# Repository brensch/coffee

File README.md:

# coffee

An espresso machine controller built emulation-first, in Rust. It's in the spirit of GaggiMate/Gaggiuino, with these differences:

- **One product, two shells.** Everything the machine does (engine, profiles, shot history, the whole HTTP API, logging) lives in the `no_std` crate `coffee-node`. The PC binary and the ESP32 firmware are thin wrappers that differ only in plumbing.
- **A physics emulator stands in for the machine.** It models the boiler and water thermals, the vibratory pump, the over-pressure valve, steam saturation, the puck, the cup and scale, and sensor quirks. It can inject faults and runs coupled in lockstep with the engine.
- **A scenario language scripts tests.** Timed and event-triggered actions, fault injection and expectations make a CI suite: 19 scenarios, about 2.5 hours of machine time in about 80 s.
- **Real-machine logs calibrate the model.** PC and firmware write the same compact binary log of the hardware boundary (`.clog`, about 2.7 bytes per tick, about 1 MB per machine-hour). `coffee-emu fit` replays it and adjusts model parameters until the simulated sensors match.
- **The web UI is all Rust (Leptos).**
  - **Machine** page: everything live from telemetry (same on the ESP32), including an animated machine diagram, shot chart, controls and temperature.
  - **Experiments**: emulator ground truth beside what the engine believes, fault injection, scenarios, model parameters.
  - Profiles, History (grind advice against a reference shot) and Settings.
  - Brewing is refused until the machine is Ready (water at temperature, group heat-soaked) unless you choose *Brew anyway*. The physical switch always works.

Target machine: **Gaggia Classic Pro E24, US 120 V / 60 Hz** only (model: `models/gaggia_classic_pro_e24_120v.toml`). See [docs/HARDWARE.md](docs/HARDWARE.md).

## Quick start

```sh
cargo build --release                       # engine, emulator, tools
(cd ui && trunk build --release)            # web UI (needs `trunk`, wasm32 target)

./target/release/coffee-emu test            # run the scenario suite
./target/release/coffee-emu serve --spawn-engine
#   -> UI at http://127.0.0.1:8080  (Experiments tab drives the emulator)
```

Other things to try:

```sh
coffee-emu run scenarios/02_shot_classic.scn --trace out/shot.csv --events
coffee-emu signals                          # everything you can read / set / fit
coffee-emu fit --log real.clog --params thermal.boiler_mass_kg,thermal.loss_boiler_w_k --out models/mine.toml
coffee-emu import-gaggimate path/to/*.json  # convert GaggiMate profiles
coffee-emu import-decent path/to/*.tcl      # convert Decent Espresso profiles
python3 tools/profile_check.py profiles/community   # brew every profile in the emulator
```

Firmware: ESP32-C6 (stable Rust), flashed and provisioned with the `coffee` CLI (non-interactive, `--json`; see [firmware/esp32/README.md](firmware/esp32/README.md)):

```sh
coffee flash                                  # build + flash over USB (needs espflash)
coffee wifi set --ssid HomeNet --password ... # store Wi-Fi, wait for an IP
open http://coffee.local/                     # the same UI and API, served by the board
coffee ota --host coffee.local                # later updates over Wi-Fi: steam rocker on, then brew held 3 s
coffee-emu capture --port /dev/ttyACM0 --out real.clog   # record its log
coffee flash --bridge && coffee-emu serve --engine-serial /dev/ttyACM0   # hardware-in-the-loop
```

## Hardware: the v45 controller board

One 71.2 × 77 mm board, the Gaggiuino split done carefully, in a printed holder that sticks to the
side panel with magnets (hardware/holder). The pump, the 3-way valve and the board's own
supply are switched on the board, behind a 7 mm milled isolation band (7.83 mm minimum, verified on the
copper). The 11 A heater stays on a factory SSR on the rear panel. It carries:
- **Mains half:** four 6.3 mm spades (N, L, P, 3), a 2 A fuse, a certified Mean Well IRM-10-5, and two
  zero-cross opto-triac channels (T435 pump, T410 valve) with X2-rated snubbers;
- an ESP32-C6-MINI-1U (105 °C rated, W.FL / MHF III antenna connector);
- a K-type thermocouple front end (MCP3421 18-bit ADC + TMP117 cold junction), plus pressure, front-panel
  (three switches in, three LEDs out) and drip-tray scale inputs;
- **latching JST GH sockets, each lead a unique size**, so no lead fits another's socket (checked on every
  build: docs/SWAP-SAFETY.md), and a screw terminal for the thermocouple;
- mains spades along the top edge, low-voltage plugs along the bottom: the two bundles leave in opposite
  directions;
- USB-C for the first flash (then updates go over Wi-Fi), and a 7-LED indicator row: status, the three
  front-panel lamps, and heater/pump/valve.

| Item | What | Notes |
|---|---|---|
| Board | v45 controller, assembled by JLCPCB (full, nothing to solder; or SMD-only plus 6 parts to solder) | `hardware/controller` generates everything: schematic, PCB, DRC, isolation check, fab and JLC files. See [docs/CIRCUIT.md](docs/CIRCUIT.md). |
| Boiler temperature | K-type M4 screw-in thermocouple (Gaggiuino's) | NIST type-K conversion with cold-junction compensation in firmware. Two-point calibration. |
| Pressure | Transducer 0–1.2 MPa, 5 V, 0.5–4.5 V, G1/4 (Gaggiuino's) + [GaggiMate plumbing kit](https://shop.gaggimate.eu/products/gaggimate-plumbing-kit) | |
| Antenna | 2.4 GHz, W.FL (MHF III) pigtail, ≤ 2.33 dBi | Outside the steel case. |
| Scale *(optional)* | Two load cells under the drip tray, dual HX711, wired | Weight stop. See docs/CALIBRATION.md. |

The full list and the reasons behind it are in [docs/HARDWARE.md](docs/HARDWARE.md); fitting it is
[docs/INSTALL.md](docs/INSTALL.md). Off-the-shelf alternatives are compared in
[docs/OFF_THE_SHELF.md](docs/OFF_THE_SHELF.md).

**Keep in the machine:** the steam thermostat (or a 165–170 °C limiter) and the thermal fuse, in
series with the heater.

## Layout

| Path | What |
|---|---|
| `crates/coffee-io` | Hardware boundary: per-mains-cycle `SensorFrame` / `ActuatorFrame` (thermocouple µV, cold junction, pressure in ADC millivolts), lockstep wire protocol. `no_std`. |
| `crates/coffee-board` | Pure firmware logic, host-tested: crystal cycle clock, ADC oversampling, switch debounce, status LED, grid-drift stroke model. `no_std`. |
| `crates/coffee-core` | The engine: sensor conversion, filters, PID + feed-forward, pump-model flow linearisation, profiles, state machine, safety. `no_std + alloc`. |
| `crates/coffee-api` | HTTP/WS API types, shot recorder, grind advice, GaggiMate importer. Shared by engine, firmware and UI. |
| `crates/coffee-node` | **The product**: engine plus shot recorder, profile library (built-ins compiled in), config, the HTTP API as a pure function, telemetry, binary log (`tlog`) and shot (`shotpack`) formats. `no_std + alloc`. |
| `crates/coffee-engine` | PC shell: lockstep link (stdio / TCP), file storage (`--data`), axum passing `/api/*` to the node, UI hosting. |
| `crates/coffee-physics` | Coupled machine model with fault injection. Parameters live in `models/*.toml`. |
| `crates/coffee-scenario` | Scenario DSL: parser and runner. |
| `crates/coffee-emu` | Emulator suite: `run`, `test`, `serve` (live lab), `replay`, `fit`, `import-gaggimate`. |
| `ui/` | Leptos web UI. |
| `hardware/controller` | Controller board as code: SKiDL schematic with isolation and pin-map checks, KiCad layout with the mains lint, Freerouting, ngspice simulations, 3D renders, JLCPCB files, audit pack. |
| `tools/` | `iterate.sh`: rebuild, run diagnostic shots, print control-quality metrics. |
| `crates/coffee-cli` | `coffee`: flash, Wi-Fi provisioning, status, logs and OTA for the board. Non-interactive, `--json`, exit codes. |
| `firmware/esp32` | ESP32-C6 firmware: machine mode (control loop, Wi-Fi, embedded UI + API, flash storage, OTA, USB console) and USB bridge mode. |
| `models/`, `profiles/`, `scenarios/` | Machine models, shot profiles (built-ins + `profiles/community`: 47 Decent and 4 GaggiMate profiles, with their own licenses), test scenarios. |

Docs: [PROFILES](docs/PROFILES.md) · [ARCHITECTURE](docs/ARCHITECTURE.md) · [HARDWARE & BOM](docs/HARDWARE.md) · [CIRCUIT](docs/CIRCUIT.md) · [OFF-THE-SHELF](docs/OFF_THE_SHELF.md) · [INSTALL](docs/INSTALL.md) · [CALIBRATION](docs/CALIBRATION.md) · [MODELS](docs/MODELS.md) · [SCENARIOS](docs/SCENARIOS.md)

## Status

- **Working and tested in emulation:**
  - engine, physics, DSL, test suite
  - calibration loop (including a test that recovers known parameters from synthetic data)
  - live lab and UI
  - GaggiMate import
- **Compiles, not yet run on hardware:** ESP32-C6 firmware: machine mode (Wi-Fi, web UI and API, WebSocket telemetry, flash storage, OTA, USB provisioning) and bridge mode; the `coffee` CLI.
- **Designed, not yet reviewed or built:** the v6 controller board (routed, DRC-checked, simulated; audit pack in `hardware/controller/build/`).
- **Not built yet:**
  - a Bluetooth scale driver
  - the motorised grinder
- **Every model parameter is an estimate until fitted to logs from your machine.** See [docs/MODELS.md](docs/MODELS.md).

⚠️ This controls a mains-powered heater and a 15 bar pump. Keep the machine's hardware thermal protection in series. See the safety section in [docs/HARDWARE.md](docs/HARDWARE.md).

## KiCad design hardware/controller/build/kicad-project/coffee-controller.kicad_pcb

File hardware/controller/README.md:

# Controller board v2

One board that drives a Gaggia Classic Pro: an ESP32-S3, the 5 V supply, zero-cross sensing,
three zero-cross triacs (heater, pump, valve), and the thermocouple and pressure inputs. The mains
side and the SELV side are split by a 7 mm copper-free band with milled slots. The design and its
calculations are in [docs/CIRCUIT.md](../../docs/CIRCUIT.md), and the install plan is in
[docs/INSTALL.md](../../docs/INSTALL.md).

## Look at it
- `build/coffee-controller-120v.kicad_pcb`: open it in KiCad 7 or later.
- `build/coffee-controller-120v.png` / `.pdf` / `-top.svg` / `-bottom.svg`: quick views.
- `build/coffee-controller-120v-drc.rpt`: DRC report. 0 errors; the warnings left are
  silkscreen overlaps, two thermal-spoke counts and one dangling stub.
- `build/coffee-controller-120v-fab/`: gerbers, drill file and pick-and-place CSV.
- `build/bom-120v.csv`: the BOM.

## Rebuild
```sh
python3 -m venv .venv && .venv/bin/pip install -r requirements.txt
.venv/bin/python controller.py            # schematic: ERC + design checks -> netlist, BOM, parts.json
source ~/opt/kienv.sh && python3 layout.py # place, route (Freerouting, 90° corners), fill, DRC, fab outputs
MAINS_V=120 .venv/bin/python controller.py && python3 layout.py --mains 120
```

`layout.py` needs:
- **KiCad 7's pcbnew Python and footprint libraries.** No root access? Extract the Ubuntu debs:
  `apt-get download kicad kicad-footprints …`, then `dpkg -x` each one, then source an env file
  that sets `PYTHONPATH`, `LD_LIBRARY_PATH` and `KICAD7_FOOTPRINT_DIR`.
- **Freerouting 2.1.0** (`fr-2.1.0.jar`, Java 21). Don't use the 2.5.0 native CLI: it hangs at
  0% CPU after an internal crash.

**Status:** generated, routed and DRC-checked by code. Not yet reviewed by a person, and not yet
built. Review the mains side before ordering.

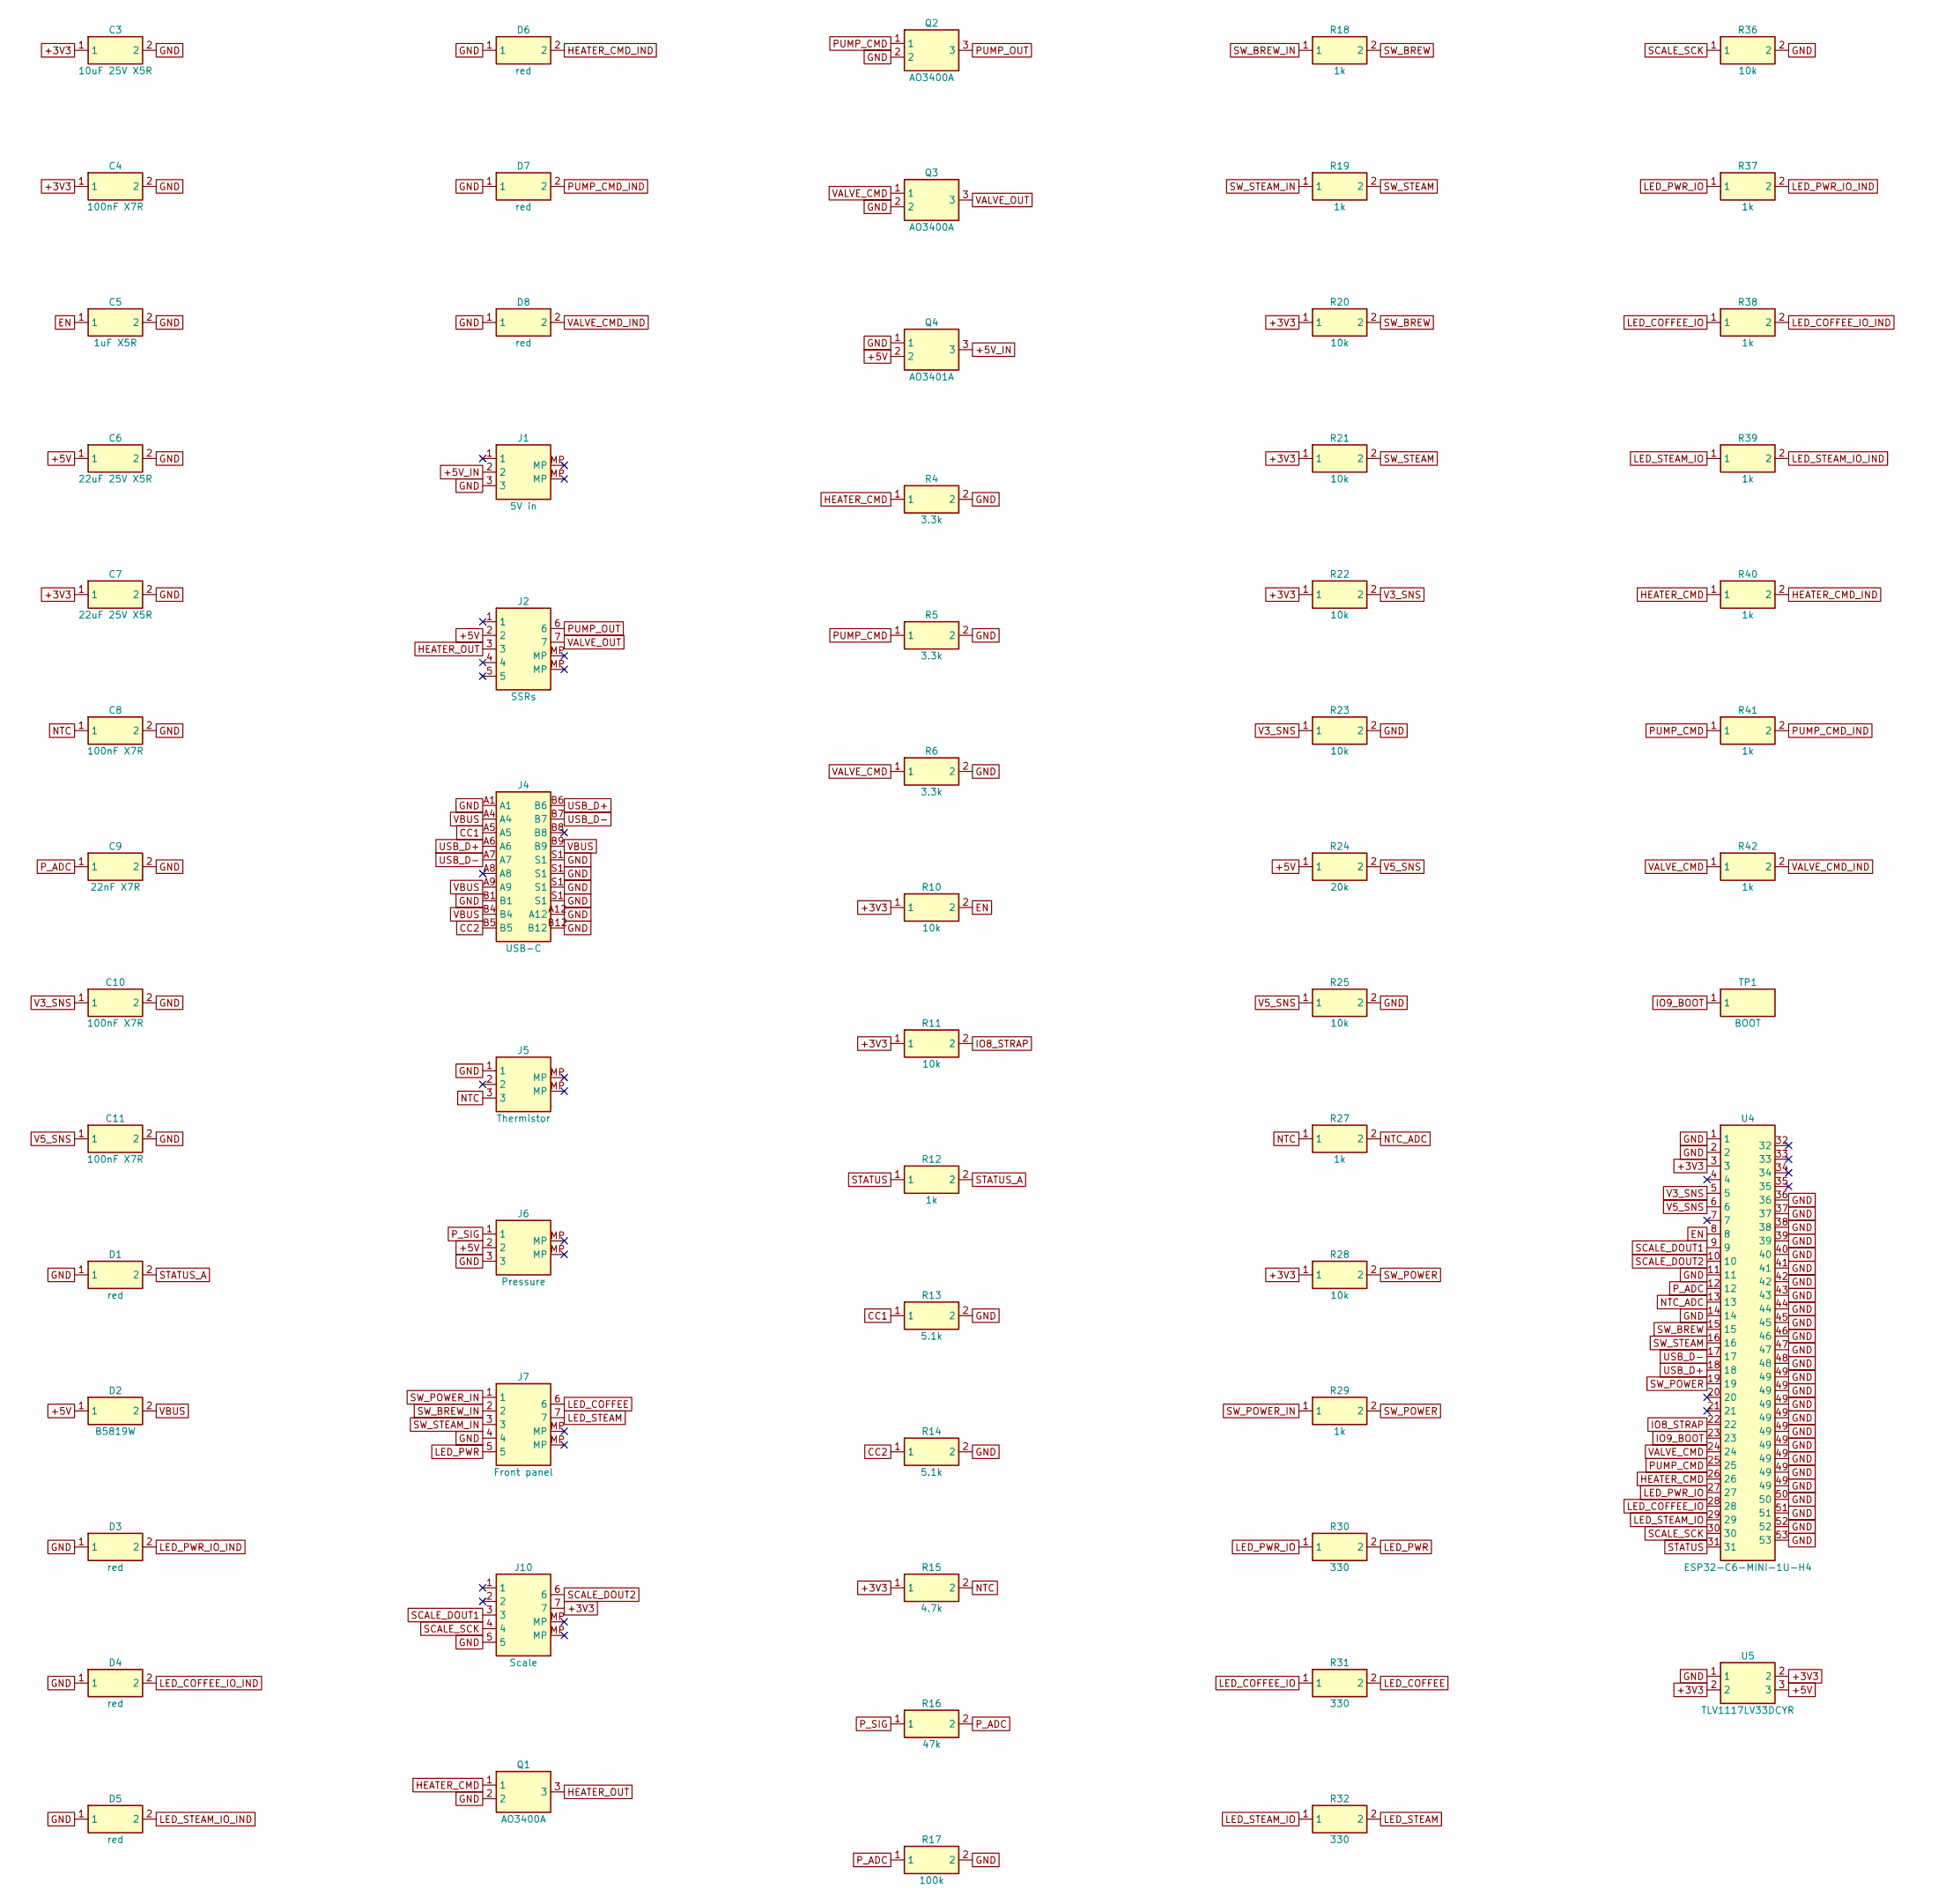
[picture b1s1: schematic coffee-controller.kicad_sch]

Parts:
C3: 10uF 25V X5R; C_0805_2012Metric
C4, C8, C10, C11: 100nF X7R; C_0603_1608Metric
C5: 1uF X5R; C_0603_1608Metric
C6, C7: 22uF 25V X5R; C_0805_2012Metric; MPN Samsung CL21A226MAQNNNE
C9: 22nF X7R; C_0603_1608Metric
D1, D3, D4, D5, D6, D7, D8: red; LED_0603_1608Metric
D2: B5819W; D_SOD-123; MPN B5819W SL
J1: 5V in; JST_GH_SM03B-GHS-TB_1x03-1MP_P1.25mm_Horizontal; MPN JST SM03B-GHS-TB
J2: SSRs; JST_GH_SM07B-GHS-TB_1x07-1MP_P1.25mm_Horizontal; MPN JST SM07B-GHS-TB
J4: USB-C; USB_C_Receptacle_HRO_TYPE-C-31-M-12; MPN HRO TYPE-C-31-M-12
J5: Thermistor; JST_GH_SM03B-GHS-TB_1x03-1MP_P1.25mm_Horizontal; MPN JST SM03B-GHS-TB
J6: Pressure; JST_GH_SM03B-GHS-TB_1x03-1MP_P1.25mm_Horizontal; MPN JST SM03B-GHS-TB
J7: Front panel; JST_GH_SM07B-GHS-TB_1x07-1MP_P1.25mm_Horizontal; MPN JST SM07B-GHS-TB
J10: Scale; JST_GH_SM07B-GHS-TB_1x07-1MP_P1.25mm_Horizontal; MPN JST SM07B-GHS-TB
Q1, Q2, Q3: AO3400A; SOT-23; MPN AO3400A
Q4: AO3401A; SOT-23; MPN AO3401A
R4, R5, R6: 3.3k; R_0603_1608Metric
R10, R11, R20, R21, R22, R23, R25, R28, R36: 10k; R_0603_1608Metric
R12, R18, R19, R27, R29, R37, R38, R39, R40, R41, R42: 1k; R_0603_1608Metric
R13, R14: 5.1k; R_0603_1608Metric
R15: 4.7k; R_0603_1608Metric
R16: 47k; R_0603_1608Metric
R17: 100k; R_0603_1608Metric
R24: 20k; R_0603_1608Metric
R30, R31, R32: 330; R_0603_1608Metric
TP1: BOOT; TestPoint_Pad_D1.0mm
U4: ESP32-C6-MINI-1U-H4; ESP32-C6-MINI-1U; MPN ESP32-C6-MINI-1U-H4
U5: TLV1117LV33DCYR; SOT-223-3_TabPin2; MPN TI TLV1117LV33DCYR

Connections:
+3V3: C3.1, C4.1, C7.1, J10.7, R10.1, R11.1, R15.1, R20.1, R21.1, R22.1, R28.1, U4.3, U5.2
+5V: C6.1, D2.1, J2.2, J6.2, Q4.2, R24.1, U5.3
+5V_IN: J1.2, Q4.3
CC1: J4.A5, R13.1
CC2: J4.B5, R14.1
EN: C5.1, R10.2, U4.8
GND: C3.2, C4.2, C5.2, C6.2, C7.2, C8.2, C9.2, C10.2, C11.2, D1.1, D3.1, D4.1, D5.1, D6.1, D7.1, D8.1, J1.3, J4.A1, J4.A12, J4.B1, J4.B12, J4.S1, J5.1, J6.3, J7.4, J10.5, Q1.2, Q2.2, Q3.2, Q4.1, R4.2, R5.2, R6.2, R13.2, R14.2, R17.2, R23.2, R25.2, R36.2, U4.1, U4.2, U4.11, U4.14, U4.36, U4.37, U4.38, U4.39, U4.40, U4.41, U4.42, U4.43, U4.44, U4.45, U4.46, U4.47, U4.48, U4.49, U4.50, U4.51, U4.52, U4.53, U5.1
HEATER_CMD: Q1.1, R4.1, R40.1, U4.26
HEATER_CMD_IND: D6.2, R40.2
HEATER_OUT: J2.3, Q1.3
IO8_STRAP: R11.2, U4.22
IO9_BOOT: TP1.1, U4.23
LED_COFFEE: J7.6, R31.2
LED_COFFEE_IO: R31.1, R38.1, U4.28
LED_COFFEE_IO_IND: D4.2, R38.2
LED_PWR: J7.5, R30.2
LED_PWR_IO: R30.1, R37.1, U4.27
LED_PWR_IO_IND: D3.2, R37.2
LED_STEAM: J7.7, R32.2
LED_STEAM_IO: R32.1, R39.1, U4.29
LED_STEAM_IO_IND: D5.2, R39.2
NTC: C8.1, J5.3, R15.2, R27.1
NTC_ADC: R27.2, U4.13
PUMP_CMD: Q2.1, R5.1, R41.1, U4.25
PUMP_CMD_IND: D7.2, R41.2
PUMP_OUT: J2.6, Q2.3
P_ADC: C9.1, R16.2, R17.1, U4.12
P_SIG: J6.1, R16.1
SCALE_DOUT1: J10.3, U4.9
SCALE_DOUT2: J10.6, U4.10
SCALE_SCK: J10.4, R36.1, U4.30
STATUS: R12.1, U4.31
STATUS_A: D1.2, R12.2
SW_BREW: R18.2, R20.2, U4.15
SW_BREW_IN: J7.2, R18.1
SW_POWER: R28.2, R29.2, U4.19
SW_POWER_IN: J7.1, R29.1
SW_STEAM: R19.2, R21.2, U4.16
SW_STEAM_IN: J7.3, R19.1
USB_D+: J4.A6, J4.B6, U4.18
USB_D-: J4.A7, J4.B7, U4.17
V3_SNS: C10.1, R22.2, R23.1, U4.5
V5_SNS: C11.1, R24.2, R25.1, U4.6
VALVE_CMD: Q3.1, R6.1, R42.1, U4.24
VALVE_CMD_IND: D8.2, R42.2
VALVE_OUT: J2.7, Q3.3
VBUS: D2.2, J4.A4, J4.A9, J4.B4, J4.B9

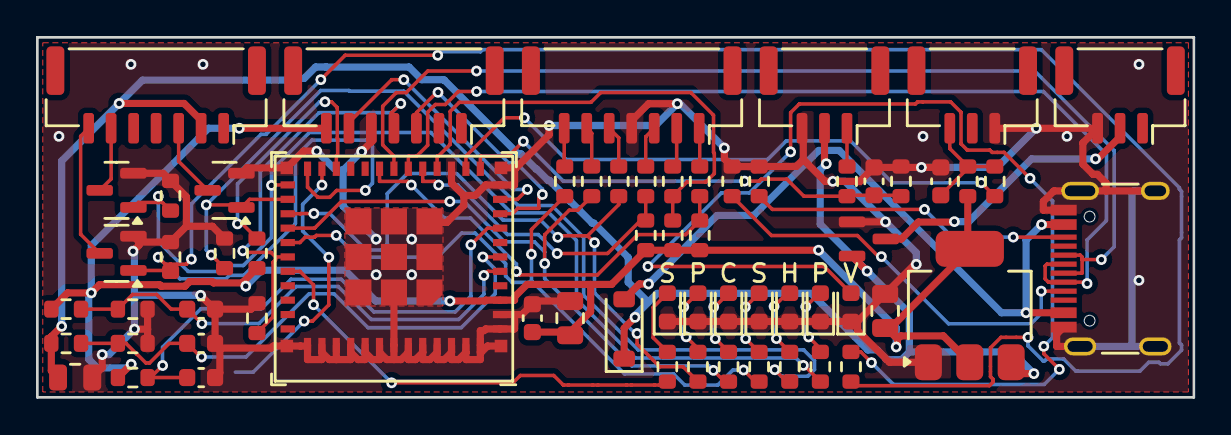
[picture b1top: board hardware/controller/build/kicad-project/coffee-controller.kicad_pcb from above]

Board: 2 copper layers, 64.2 x 20.0 mm, 63 parts (1 on the bottom side), 47 nets.

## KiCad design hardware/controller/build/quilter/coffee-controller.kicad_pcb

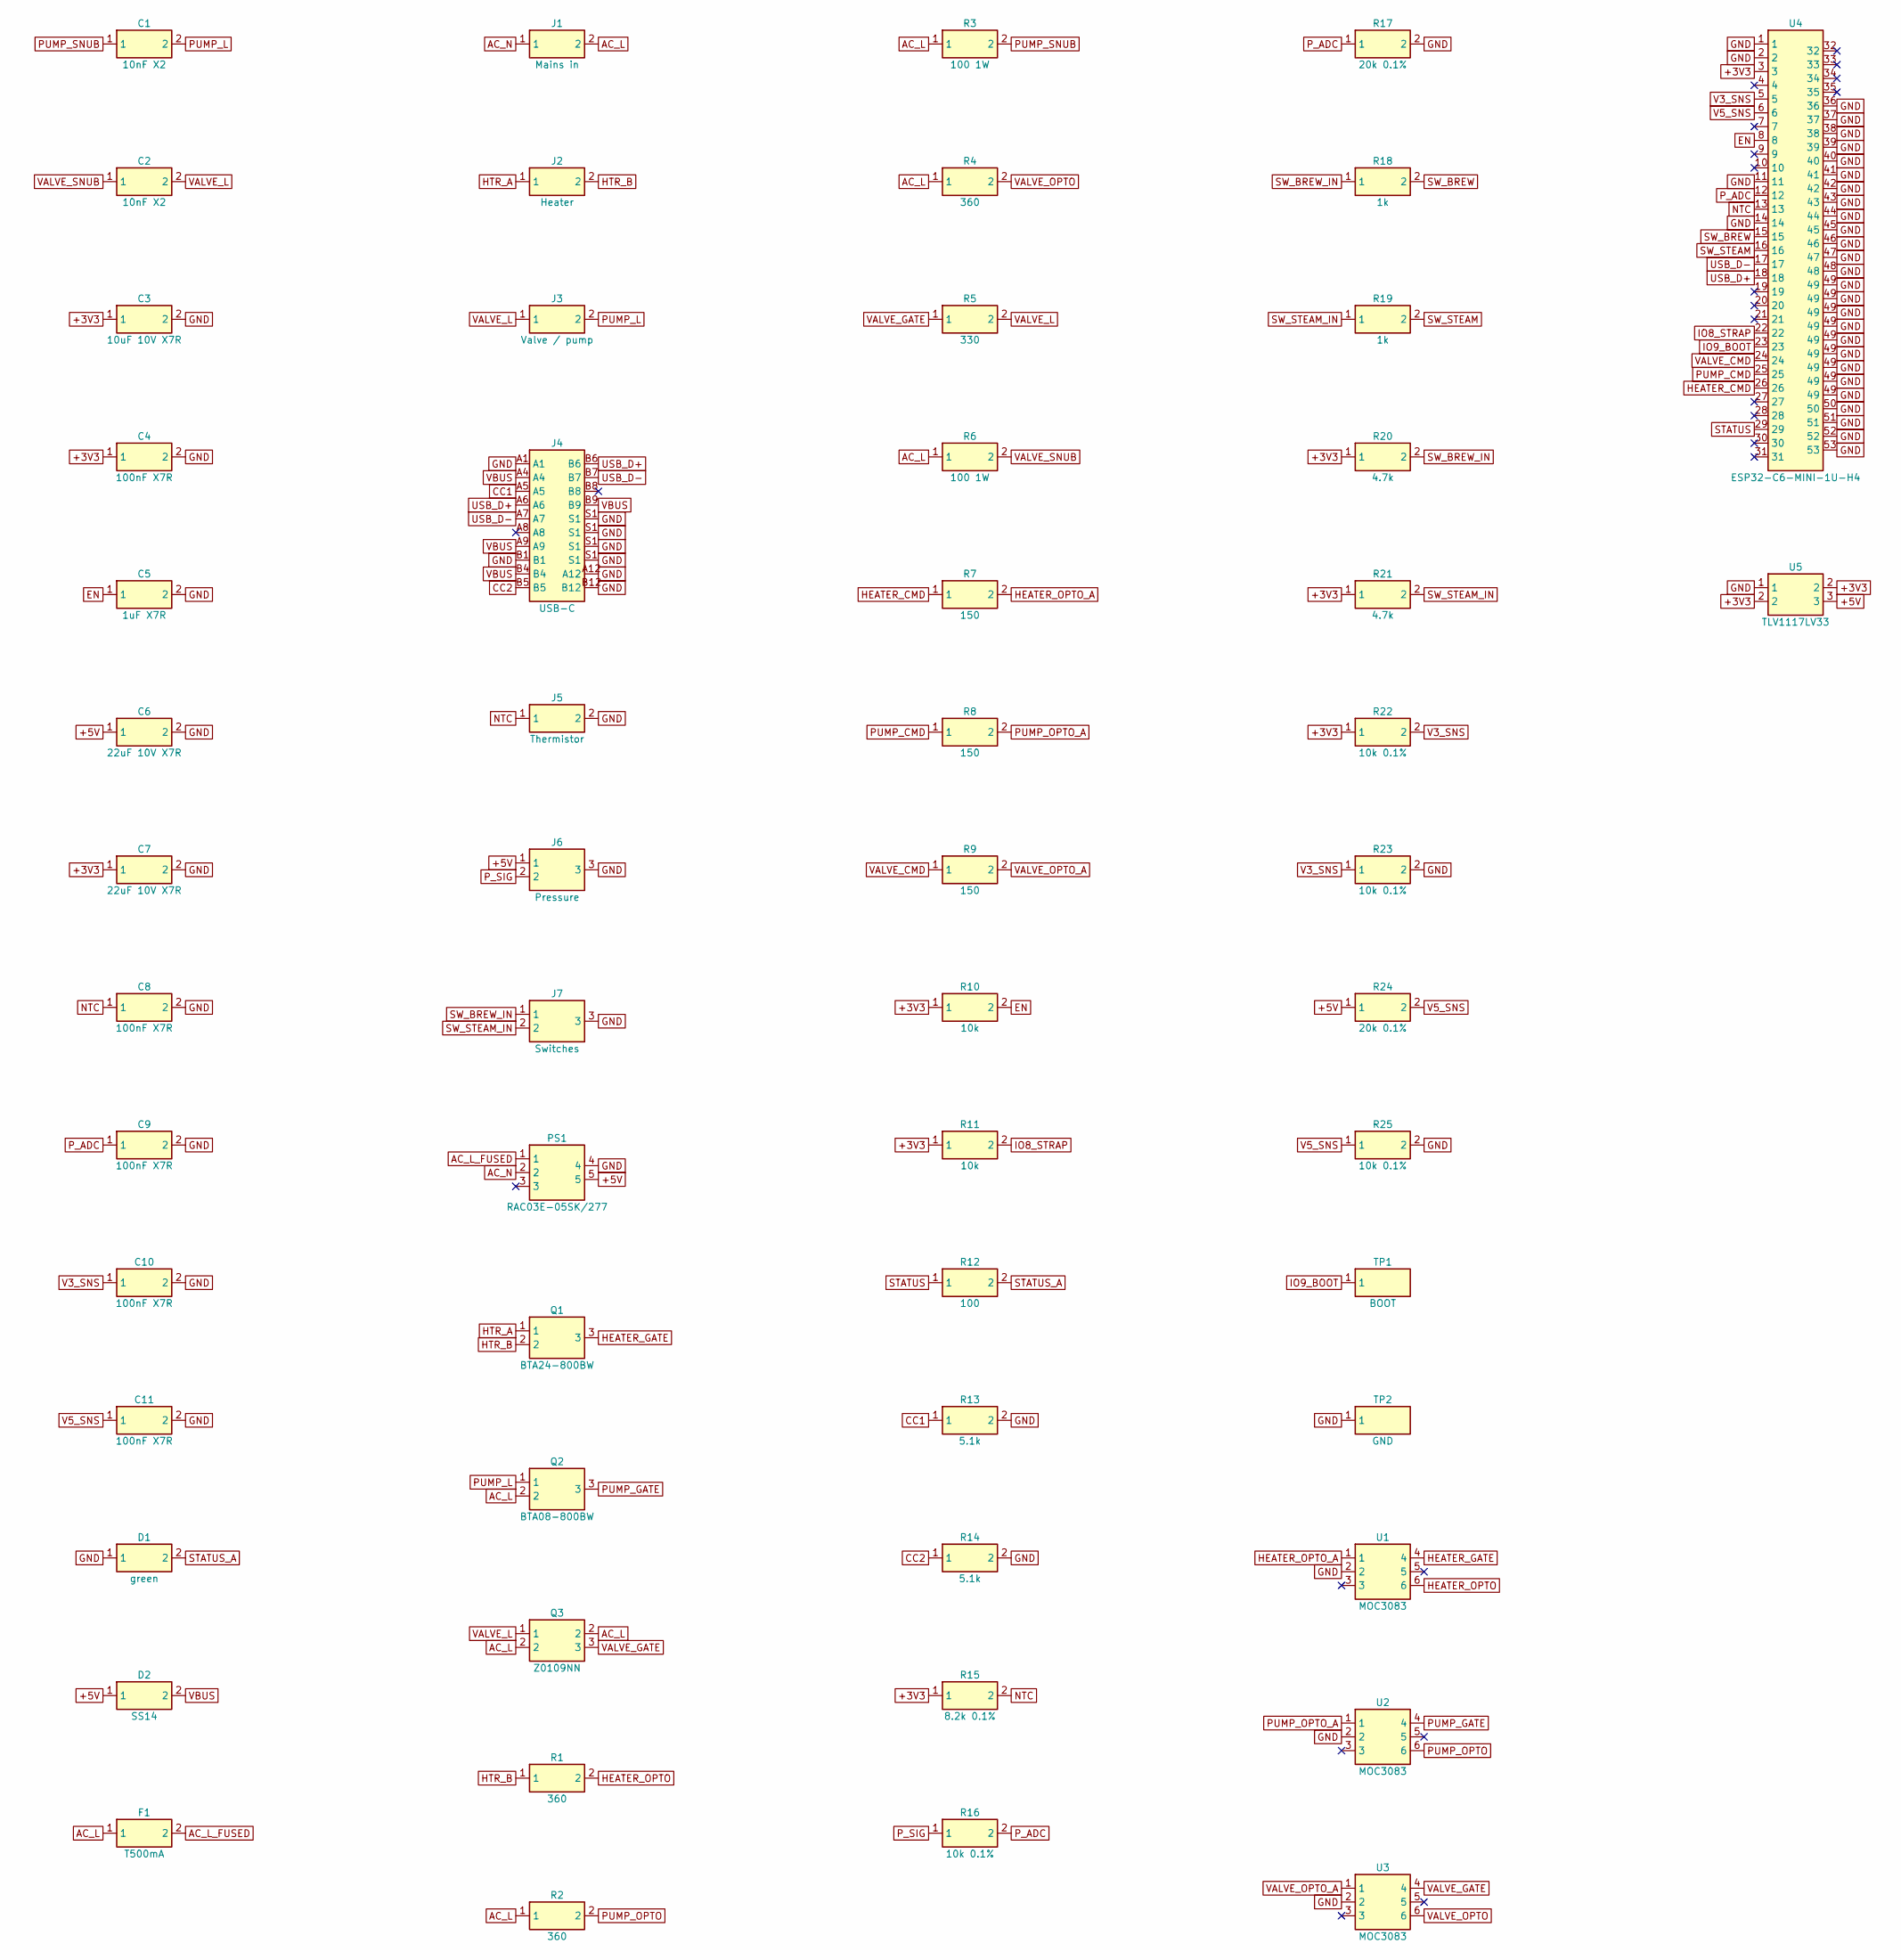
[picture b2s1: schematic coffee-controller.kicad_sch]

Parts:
C1, C2: 10nF X2; C_2220_Murata_GA355; MPN Murata GA355QR7GB103KW01L (10 nF X2 250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
C3: 10uF 10V X7R; C_0805_2012Metric
C4, C8, C9, C10, C11: 100nF X7R; C_0603_1608Metric
C5: 1uF X7R; C_0603_1608Metric
C6, C7: 22uF 10V X7R; C_0805_2012Metric; MPN Murata GRM21BZ71A226ME15L
D1: green; LED_0603_1608Metric
D2: SS14; D_SMA; MPN SS14
F1: T500mA; Fuse_Littelfuse_372_D8.50mm; MPN Littelfuse 37205000411 (TR5, 500 mA slo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
J1: Mains in; TerminalBlock_Phoenix_MKDS-1,5-2-5.08_1x02_P5.08mm_Horizont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; MPN Phoenix Contact MKDS 1,5/2-5.08 (171572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
J2: Heater; TerminalBlock_Phoenix_MKDS-3-2-5.08_1x02_P5.08mm_Horizontal; MPN Phoenix Contact MKDS 3/2-5.08 (1711725)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
J3: Valve / pump; TerminalBlock_Phoenix_MKDS-1,5-2-5.08_1x02_P5.08mm_Horizont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; MPN Phoenix Contact MKDS 1,5/2-5.08 (171572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
J4: USB-C; USB_C_Receptacle_GCT_USB4105-xx-A_16P_TopMnt_Horizontal; MPN GCT USB4105-GF-A
J5: Thermistor; JST_PH_B2B-PH-K_1x02_P2.00mm_Vertical
J6: Pressure; JST_PH_B3B-PH-K_1x03_P2.00mm_Vertical
J7: Switches; JST_PH_B3B-PH-K_1x03_P2.00mm_Vertical
PS1: RAC03E-05SK/277; RAC03E-K_277; MPN RECOM RAC03E-05SK/277
Q1: BTA24-800BW; TO-220-3_Vertical_Drill1.2; MPN ST BTA24-800BWRG (25 A, 800 V, insulate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
Q2: BTA08-800BW; TO-220-3_Vertical_Drill1.2; MPN ST BTA08-800BWRG (8 A, 800 V, insulated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
Q3: Z0109NN; SOT-223-3_TabPin2; MPN ST Z0109NN5AA4 (1 A, 800 V, IGT 10 mA)
R1, R2, R4: 360; R_1206_3216Metric
R3, R6: 100 1W; R_2512_6332Metric
R5: 330; R_1206_3216Metric
R7, R8, R9: 150; R_0603_1608Metric
R10, R11: 10k; R_0603_1608Metric
R12: 100; R_0603_1608Metric
R13, R14: 5.1k; R_0603_1608Metric
R15: 8.2k 0.1%; R_0603_1608Metric
R16, R22, R23, R25: 10k 0.1%; R_0603_1608Metric
R17, R24: 20k 0.1%; R_0603_1608Metric
R18, R19: 1k; R_0603_1608Metric
R20, R21: 4.7k; R_0603_1608Metric
TP1: BOOT; TestPoint_Pad_D1.5mm
TP2: GND; TestPoint_Pad_D1.5mm
U1, U2, U3: MOC3083; DIP-6_W10.16mm; MPN onsemi MOC3083TVM (0.4" leads)
U4: ESP32-C6-MINI-1U-H4; ESP32-C6-MINI-1U; MPN ESP32-C6-MINI-1U-H4
U5: TLV1117LV33; SOT-223-3_TabPin2; MPN TI TLV1117LV33DCYR

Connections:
+3V3: C3.1, C4.1, C7.1, R10.1, R11.1, R15.1, R20.1, R21.1, R22.1, U4.3, U5.2
+5V: C6.1, D2.1, J6.1, PS1.5, R24.1, U5.3
AC_L: F1.1, J1.2, Q2.2, Q3.2, R2.1, R3.1, R4.1, R6.1
AC_L_FUSED: F1.2, PS1.1
AC_N: J1.1, PS1.2
CC1: J4.A5, R13.1
CC2: J4.B5, R14.1
EN: C5.1, R10.2, U4.8
GND: C3.2, C4.2, C5.2, C6.2, C7.2, C8.2, C9.2, C10.2, C11.2, D1.1, J4.A1, J4.A12, J4.B1, J4.B12, J4.S1, J5.2, J6.3, J7.3, PS1.4, R13.2, R14.2, R17.2, R23.2, R25.2, TP2.1, U1.2, U2.2, U3.2, U4.1, U4.2, U4.11, U4.14, U4.36, U4.37, U4.38, U4.39, U4.40, U4.41, U4.42, U4.43, U4.44, U4.45, U4.46, U4.47, U4.48, U4.49, U4.50, U4.51, U4.52, U4.53, U5.1
HEATER_CMD: R7.1, U4.26
HEATER_GATE: Q1.3, U1.4
HEATER_OPTO: R1.2, U1.6
HEATER_OPTO_A: R7.2, U1.1
HTR_A: J2.1, Q1.1
HTR_B: J2.2, Q1.2, R1.1
IO8_STRAP: R11.2, U4.22
IO9_BOOT: TP1.1, U4.23
NTC: C8.1, J5.1, R15.2, U4.13
PUMP_CMD: R8.1, U4.25
PUMP_GATE: Q2.3, U2.4
PUMP_L: C1.2, J3.2, Q2.1
PUMP_OPTO: R2.2, U2.6
PUMP_OPTO_A: R8.2, U2.1
PUMP_SNUB: C1.1, R3.2
P_ADC: C9.1, R16.2, R17.1, U4.12
P_SIG: J6.2, R16.1
STATUS: R12.1, U4.29
STATUS_A: D1.2, R12.2
SW_BREW: R18.2, U4.15
SW_BREW_IN: J7.1, R18.1, R20.2
SW_STEAM: R19.2, U4.16
SW_STEAM_IN: J7.2, R19.1, R21.2
USB_D+: J4.A6, J4.B6, U4.18
USB_D-: J4.A7, J4.B7, U4.17
V3_SNS: C10.1, R22.2, R23.1, U4.5
V5_SNS: C11.1, R24.2, R25.1, U4.6
VALVE_CMD: R9.1, U4.24
VALVE_GATE: Q3.3, R5.1, U3.4
VALVE_L: C2.2, J3.1, Q3.1, R5.2
VALVE_OPTO: R4.2, U3.6
VALVE_OPTO_A: R9.2, U3.1
VALVE_SNUB: C2.1, R6.2
VBUS: D2.2, J4.A4, J4.A9, J4.B4, J4.B9

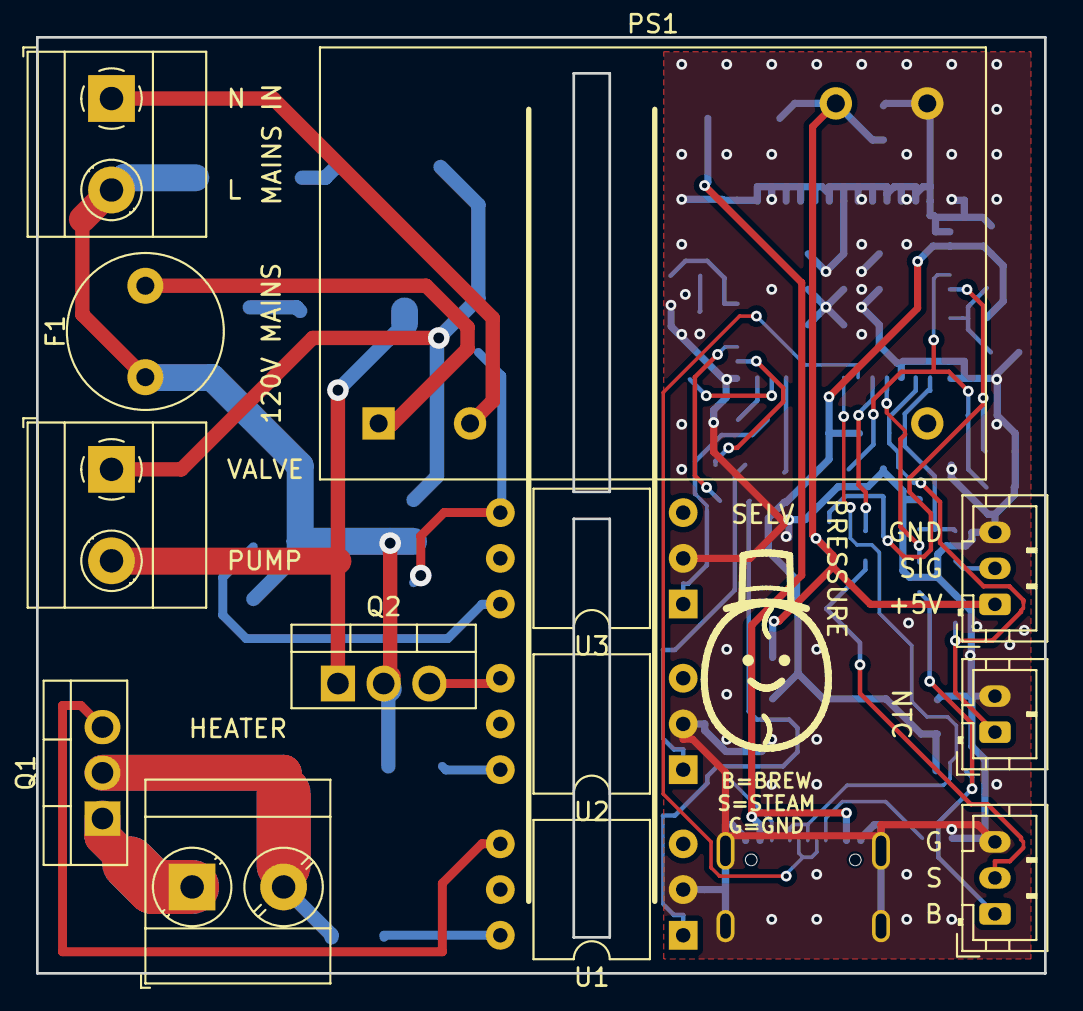
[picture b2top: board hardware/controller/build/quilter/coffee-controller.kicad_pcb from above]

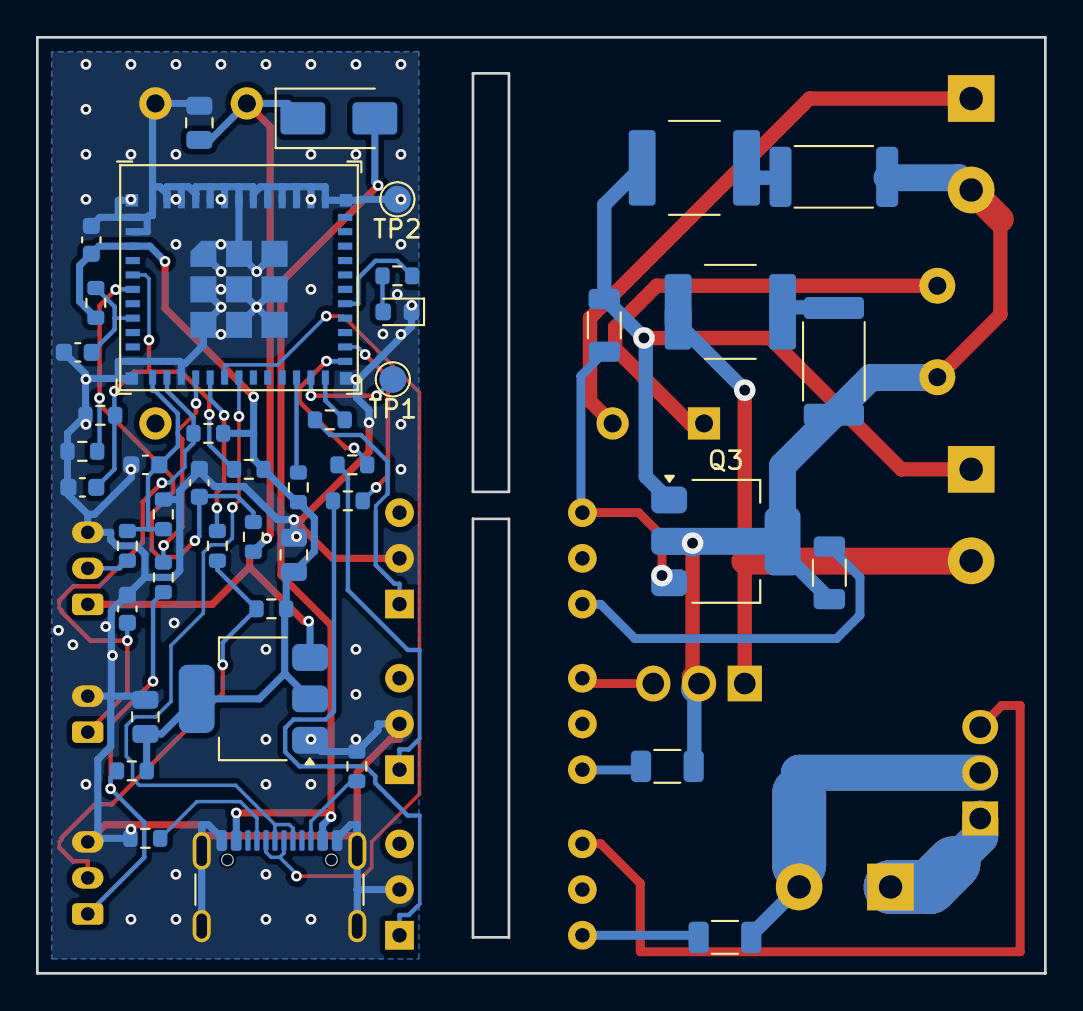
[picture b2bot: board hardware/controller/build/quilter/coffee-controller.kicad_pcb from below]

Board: 2 copper layers, 56.0 x 52.0 mm, 57 parts (44 on the bottom side), 43 nets.
